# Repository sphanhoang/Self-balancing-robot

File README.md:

# Self-Balancing Robot with ESP32 and MPU6050

A comprehensive self-balancing robot implementation using ESP32 NodeMCU-32S board with GY-521 MPU6050 module, featuring FreeRTOS multi-tasking architecture, DMP (Digital Motion Processor) sensor fusion, and a real-time web interface for parameter tuning.

## 🚀 Features

- **FreeRTOS Multi-tasking Architecture**: Separate tasks for sensor reading, control, motor control, encoder reading, and web server
- **MPU6050 DMP Mode**: Uses Digital Motion Processor for accurate attitude estimation with quaternion-based sensor fusion
- **Dual PID Control System**: Roll (angle) and speed PID controllers with real-time parameter tuning
- **Real-time Web Interface**: Live parameter adjustment, data visualization, and robot control via WiFi
- **Encoder Feedback**: Quadrature encoder support for precise motor speed measurement
- **Safety Features**: Emergency stop, angle limits, and integral windup protection
- **Modular Design**: Easy to extend and modify with clear separation of concerns

## 📋 Hardware Requirements

### Main Components
- **ESP32 NodeMCU-32S** development board
- **GY-521 MPU6050** IMU module
- **Motor Driver** (L298N, TB6612FNG, or similar)
- **2x DC Motors** with quadrature encoders
- **Battery Pack** (7.4V - 12V recommended)
- **Robot Chassis** (3D printed or custom)

### Pin Connections

| ESP32 Pin | Component | Function |
|-----------|-----------|----------|
| GPIO 21   | MPU6050   | SDA (I2C) |
| GPIO 22   | MPU6050   | SCL (I2C) |
| GPIO 14   | Motor Driver | ENA (Right Motor PWM) |
| GPIO 32   | Motor Driver | ENB (Left Motor PWM) |
| GPIO 27   | Motor Driver | IN1 (Right Motor Direction) |
| GPIO 26   | Motor Driver | IN2 (Right Motor Direction) |
| GPIO 25   | Motor Driver | IN3 (Left Motor Direction) |
| GPIO 33   | Motor Driver | IN4 (Left Motor Direction) |
| GPIO 16   | Left Encoder | Channel A |
| GPIO 17   | Left Encoder | Channel B |
| GPIO 18   | Right Encoder | Channel A |
| GPIO 19   | Right Encoder | Channel B |

## 🏗️ Software Architecture

### FreeRTOS Task Structure

```
┌─────────────────┐    ┌─────────────────┐    ┌─────────────────┐
│   Sensor Task   │───▶│  Control Task   │───▶│   Motor Task    │
│   (Priority 5)  │    │  (Priority 4)   │    │  (Priority 3)   │
│  100Hz reading  │    │  100Hz control  │    │  100Hz update   │
└─────────────────┘    └─────────────────┘    └─────────────────┘
         │                       │                       │
         ▼                       ▼                       ▼
┌─────────────────┐    ┌─────────────────┐    ┌─────────────────┐
│  MPU6050 DMP    │    │  PID Controllers│    │  Motor Drivers  │
│  Sensor Fusion  │    │  Roll & Speed   │    │  PWM Control    │
└─────────────────┘    └─────────────────┘    └─────────────────┘
         │                       │                       │
         ▼                       ▼                       ▼
┌─────────────────┐    ┌─────────────────┐    ┌─────────────────┐
│  Encoder Task   │    │  Web Server     │    │  Monitor Task   │
│  (Priority 3)   │    │  (Priority 2)   │    │  (Priority 1)   │
│  1Hz reading    │    │  WiFi + HTTP    │    │  0.5Hz logging  │
└─────────────────┘    └─────────────────┘    └─────────────────┘
```

### Key Components

1. **Sensor Task**: Reads MPU6050 data using DMP mode with quaternion fusion
2. **Control Task**: Implements dual PID control (roll angle + speed) with web parameter updates
3. **Motor Task**: Controls motor speeds via MCPWM with direction control
4. **Encoder Task**: Reads quadrature encoders and calculates motor speeds
5. **Web Server Task**: Provides real-time web interface for parameter tuning and monitoring
6. **Monitor Task**: Logs system status and debugging information

## 🔧 Configuration

### PID Parameters (Tune for your robot)

```cpp
// Roll control (primary balancing)
#define KP_ROLL 18.0f     // Proportional gain (best results: 18)
#define KI_ROLL 50.0f     // Integral gain (best results: 50)
#define KD_ROLL 0.4f      // Derivative gain (best results: 0.4)

// Speed control (for forward/backward movement)
#define KP_SPEED 0.01f    // Proportional gain
#define KI_SPEED 0.01f    // Integral gain
#define KD_SPEED 0.01f    // Derivative gain
#define TILT_ANGLE 0.6f   // Target tilt angle for speed control
```

### Safety Limits

```cpp
#define MAX_MOTOR_SPEED 255.0f        // Maximum PWM value
#define MIN_MOTOR_SPEED 30.0f         // Minimum PWM value (38.25)
#define MAX_ANGLE 15.0f               // Normal operation limit (degrees)
#define MIN_ANGLE -15.0f              // Normal operation limit (degrees)
#define PWM_FREQ_HZ 100               // PWM frequency
```

### Web Interface Configuration

```cpp
#define CONFIG_WIFI_SSID "your_wifi_ssid"
#define CONFIG_WIFI_PASSWORD "your_wifi_password"
#define WEB_SERVER_PORT 80
```

## 🚀 Getting Started

### 1. Hardware Setup

1. **Connect MPU6050**:
   - VCC → 3.3V
   - GND → GND
   - SDA → GPIO 21
   - SCL → GPIO 22

2. **Connect Motor Driver**:
   - Connect motors to motor driver
   - Connect PWM and DIR pins to ESP32
   - Connect power supply

3. **Mount Components**:
   - Securely mount MPU6050 on robot chassis
   - Ensure MPU6050 is level when robot is balanced
   - Mount motors and wheels

### 2. Software Setup

1. **Install PlatformIO** (if not already installed)

2. **Clone/Download** this project

3. **Configure WiFi** (in `src/web_interface.cpp`):
   ```cpp
   #define CONFIG_WIFI_SSID "your_wifi_ssid"
   #define CONFIG_WIFI_PASSWORD "your_wifi_password"
   ```

4. **Build and Upload**:
   ```bash
   pio run -t upload
   ```

5. **Monitor Output**:
   ```bash
   pio device monitor
   ```

6. **Access Web Interface**:
   - Look for the IP address in the serial monitor output
   - Open your browser and navigate to `http://[robot_ip_address]`

### 3. Calibration

The system uses pre-calibrated MPU6050 offsets. You'll see:
```
I (xxxx) MPU6050: Testing device connections...
I (xxxx) MPU6050: MPU6050 connection successful
I (xxxx) MPU6050: Initializing DMP...
I (xxxx) MPU6050: DMP is ready!
```

## 🎛️ Tuning Guide

### Step 1: Basic Roll Control
1. Start with **KP_ROLL = 15.0f**
2. Gradually increase until robot shows response
3. Add **KD_ROLL = 0.3f** to reduce oscillations
4. Fine-tune for stability

### Step 2: Web Interface Tuning
1. Connect to the robot's web interface
2. Use the real-time sliders to adjust PID parameters
3. Monitor the live data chart for system response
4. Enable/disable balancing with the control button

### Step 3: Speed Control (Optional)
1. The system includes encoder feedback for speed control
2. Tune **KP_SPEED**, **KI_SPEED**, **KD_SPEED** for smooth movement
3. Adjust **TILT_ANGLE** for desired forward/backward tilt

### Step 4: Safety Tuning
1. Adjust **MAX_ANGLE** and **MIN_ANGLE** based on your robot's limits
2. Set appropriate **MIN_MOTOR_SPEED** to prevent stalling
3. Monitor the system through the web interface

## 🌐 Web Interface

The robot includes a comprehensive web interface accessible via WiFi:

### Features
- **Real-time Data Visualization**: Live charts showing angle and PID output
- **Parameter Tuning**: Sliders for adjusting PID parameters in real-time
- **Robot Control**: Enable/disable balancing with a single click
- **Status Monitoring**: Current angle, output values, and system status

### Access
1. Connect to the same WiFi network as configured in the code
2. Open your browser and navigate to the robot's IP address
3. Use the interface to tune parameters and monitor performance

### API Endpoints
- `GET /` - Main web interface
- `GET /data` - JSON data for real-time updates
- `GET /pid?kp_r=X&ki_r=Y&kd_r=Z` - Update PID parameters
- `GET /control?enable=1` - Enable/disable balancing

## 📊 Data Flow

### Sensor Data Structure
```cpp
typedef struct {
    float yaw, pitch, roll;        // Euler angles (degrees)
    float accel_x, accel_y, accel_z; // Linear acceleration (g)
    uint32_t timestamp;             // System timestamp
    float dt_since_last;            // Time delta since last reading
} sensor_data_t;
```

### Control Data Structure
```cpp
typedef struct {
    float roll_output;              // Roll PID output
    float speed_output;             // Speed PID output
    float left_motor_speed;         // Left motor PWM (-255 to 255)
    float right_motor_speed;        // Right motor PWM (-255 to 255)
    float left_motor_feedback;      // Left motor speed feedback (RPS)
    float right_motor_feedback;     // Right motor speed feedback (RPS)
    uint32_t timestamp;             // System timestamp
} control_data_t;
```

### Encoder Data Structure
```cpp
typedef struct {
    uint32_t left_encoder_pulseCount;   // Left encoder pulse count
    uint32_t right_encoder_pulseCount;  // Right encoder pulse count
    float left_motor_speed;             // Left motor speed (RPS)
    float right_motor_speed;            // Right motor speed (RPS)
} encoder_data_t;
```

### Web Control Structure
```cpp
typedef struct {
    float kp_roll, ki_roll, kd_roll;    // Roll PID parameters
    float kp_speed, ki_speed, kd_speed; // Speed PID parameters
    bool enable_balance;                 // Balance enable flag
    float target_angle;                  // Target tilt angle
} web_control_t;
```

## 🔍 Debugging

### Monitor Output
The system provides detailed logging:
```
I (xxxx) MPU: MPU6050 connection successful
I (xxxx) MPU: DMP is ready!
I (xxxx) WEB: Connect to: http://192.168.1.100
motor rps: LEFT: 2.1   RIGHT: 2.3
```

### Common Issues

1. **Robot falls immediately**:
   - Check MPU6050 orientation and mounting
   - Verify motor connections and polarity
   - Increase KP_ROLL gradually (start with 15.0)
   - Check if motors are responding correctly

2. **Oscillations**:
   - Reduce KP_ROLL
   - Increase KD_ROLL
   - Check for mechanical issues (loose connections)
   - Verify encoder readings are stable

3. **No response**:
   - Verify I2C connection (SDA/SCL pins)
   - Check motor driver power supply
   - Ensure proper WiFi configuration
   - Check serial monitor for error messages

4. **Web interface not accessible**:
   - Verify WiFi credentials in `web_interface.cpp`
   - Check if robot connected to WiFi (look for IP address in logs)
   - Ensure you're on the same network as the robot

5. **Encoder issues**:
   - Check encoder wiring (A/B channels)
   - Verify pull-up resistors are working
   - Check if encoder counts are incrementing in monitor output

## 🔌 PCB Design

The project includes a custom breakout board design in KiCad:

### Features
- **ESP32 NodeMCU-32S** mounting
- **MPU6050** module socket
- **Motor driver** connections (L298N compatible)
- **Encoder** input connectors
- **Power management** with voltage regulation
- **Debug headers** for easy testing

### Files
- `BreakoutBoard.kicad_pcb` - Main PCB layout
- `BreakoutBoard.kicad_sch` - Schematic design
- `Gerbers/` - Manufacturing files ready for PCB fabrication

### Usage
1. Order PCBs using the Gerber files
2. Solder components according to the schematic
3. Mount the ESP32 and MPU6050 modules
4. Connect motors and encoders to the appropriate headers

## 🛠️ Customization

### Adding Features

1. **Bluetooth Control**:
   - Add Bluetooth task alongside web server
   - Implement command parsing for mobile apps
   - Modify control task to accept external commands

2. **Enhanced Web Interface**:
   - Add data logging capabilities
   - Implement parameter persistence to flash
   - Add more sensor data visualization

3. **Data Logging**:
   - Add SD card support for data recording
   - Log sensor data for analysis
   - Export for MATLAB/Python analysis

4. **Advanced Control**:
   - Implement path following algorithms
   - Add obstacle avoidance
   - Implement remote control via web interface

### Motor Driver Support

The code supports various motor drivers through the `set_motor_speed()` function:

```cpp
void set_motor_speed(int motor, float speed) {
    // Current implementation supports L298N-style drivers
    // Easily adaptable for TB6612FNG, DRV8833, etc.
    // motor: 0 = right, 1 = left
    // speed: -255 to 255 (PWM value)
}
```

## 📚 Technical Details

### MPU6050 DMP Mode
- **Sample Rate**: 100Hz sensor reading
- **Fusion Algorithm**: Quaternion-based sensor fusion with gravity compensation
- **Output**: Direct Euler angles (yaw, pitch, roll) and linear acceleration
- **Calibration**: Pre-calibrated offsets for stable operation
- **DMP Features**: Built-in sensor fusion, FIFO buffer, interrupt support

### PID Control
- **Roll Control**: Primary balancing control using roll angle
- **Speed Control**: Forward/backward movement with encoder feedback
- **Anti-windup**: Integral term clamping to prevent windup
- **Derivative Filtering**: Prevents noise amplification
- **Real-time Tuning**: Parameters adjustable via web interface

### FreeRTOS Features
- **Task Priorities**: Sensor(5) > Control(4) > Motor(3) > Encoder(3) > Web(2) > Monitor(1)
- **Inter-task Communication**: Mutexes for data protection
- **Real-time Scheduling**: Deterministic timing with vTaskDelayUntil
- **Memory Management**: Optimized stack sizes for each task
- **Core Assignment**: All tasks run on Core 1 for consistency

### Motor Control
- **PWM Generation**: MCPWM hardware for precise motor control
- **Direction Control**: GPIO-based direction switching
- **Speed Range**: 30-255 PWM values with deadband protection
- **Encoder Feedback**: Quadrature encoder reading with interrupt handling

### Web Interface
- **HTTP Server**: Lightweight web server for parameter control
- **Real-time Updates**: 100ms refresh rate for live data
- **JSON API**: RESTful endpoints for data exchange
- **Responsive Design**: Works on desktop and mobile devices

## 🤝 Contributing

1. Fork the repository
2. Create a feature branch
3. Make your changes
4. Test thoroughly
5. Submit a pull request

## 📄 License

This project is open source. Feel free to use, modify, and distribute.

## 🙏 Acknowledgments

- **Jeff Rowberg** for the excellent MPU6050 library and DMP implementation
- **ESP-IDF** team for the robust FreeRTOS implementation and ESP32 support
- **InvenSense** for the MPU6050 sensor and DMP technology
- **PlatformIO** team for the excellent development environment
- **KiCad** community for the open-source PCB design tools

## 📞 Support

For questions and support:
- Check the debugging section above
- Review the code comments
- Open an issue on GitHub

---

**Happy Balancing! 🤖⚖️**

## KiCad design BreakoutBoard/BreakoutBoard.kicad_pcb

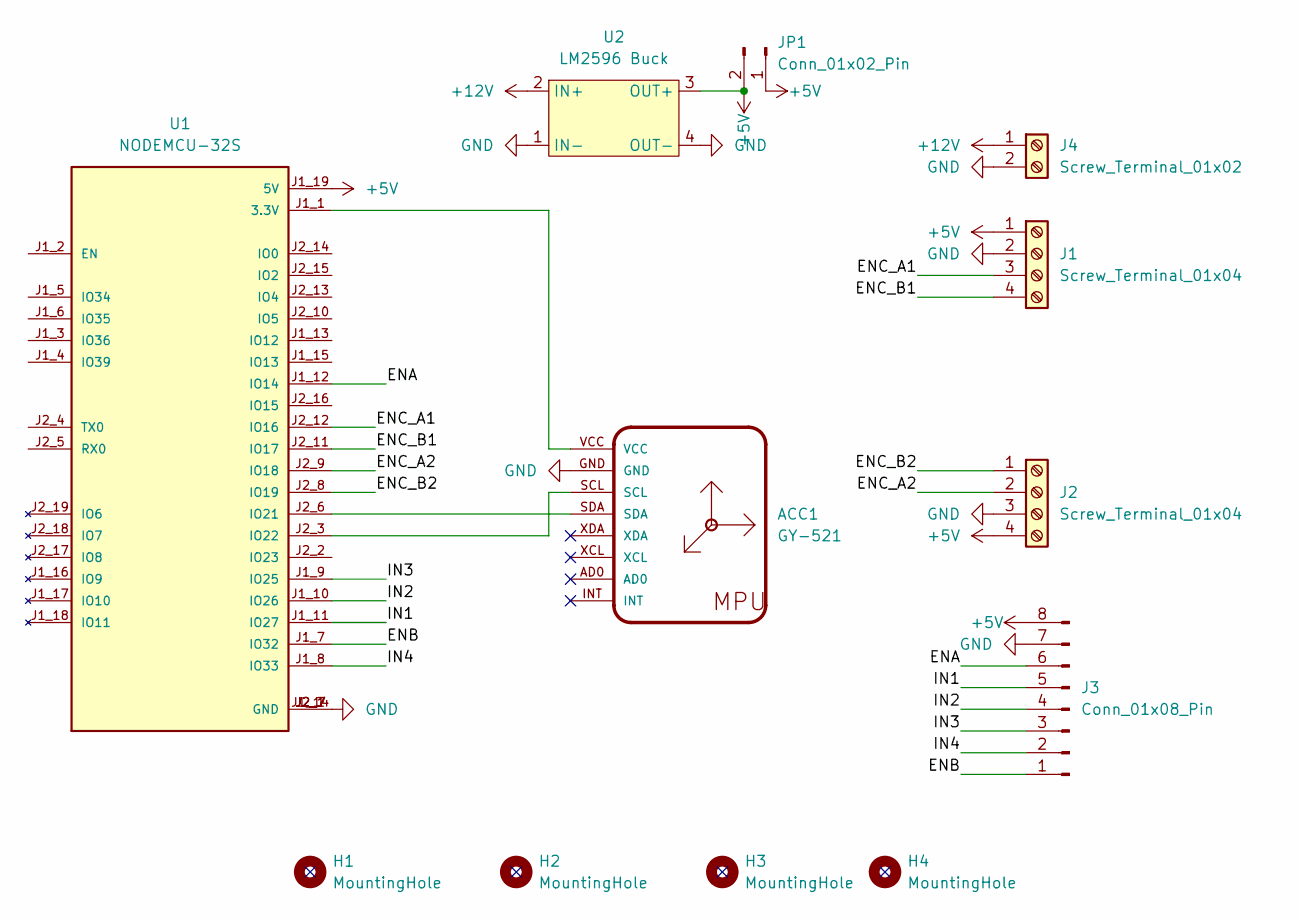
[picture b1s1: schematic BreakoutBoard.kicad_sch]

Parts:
ACC1: GY-521
H1, H2, H3, H4: MountingHole; MountingHole_3.2mm_M3_Pad
J1, J2: Screw_Terminal_01x04; ScrewTerminal_TB007-508-04BE
J3: Conn_01x08_Pin; PinHeader_1x08_P2.54mm_Vertical
J4: Screw_Terminal_01x02; ScrewTerminal_TB007-508-02BE
JP1: Conn_01x02_Pin; PinHeader_1x02_P2.54mm_Vertical
U1: NODEMCU-32S; ESP32-NODEMCU-32S; PARTREV V1
U2: LM2596 Buck; LM2596 WC00100 Module

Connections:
+5V: J1.1, J2.4, J3.8, JP1.1, JP1.2, U1.J1_19 (5V), U2.3 (OUT+)
+12V: J4.1, U2.2 (IN+)
/ENA: J3.6, U1.J1_12 (IO14)
/ENB: J3.1, U1.J1_7 (IO32)
/ENC_A1: J1.3, U1.J2_12 (IO16)
/ENC_A2: J2.2, U1.J2_9 (IO18)
/ENC_B1: J1.4, U1.J2_11 (IO17)
/ENC_B2: J2.1, U1.J2_8 (IO19)
/IN1: J3.5, U1.J1_11 (IO27)
/IN2: J3.4, U1.J1_10 (IO26)
/IN3: J3.3, U1.J1_9 (IO25)
/IN4: J3.2, U1.J1_8 (IO33)
GND: ACC1.GND, J1.2, J2.3, J3.7, J4.2, U1.J1_14 (GND), U1.J2_1 (GND), U1.J2_7 (GND), U2.1 (IN-), U2.4 (OUT-)
unnamed: ACC1.VCC, U1.J1_1 (3.3V)
unnamed: ACC1.SDA, U1.J2_6 (IO21)
unnamed: ACC1.SCL, U1.J2_3 (IO22)

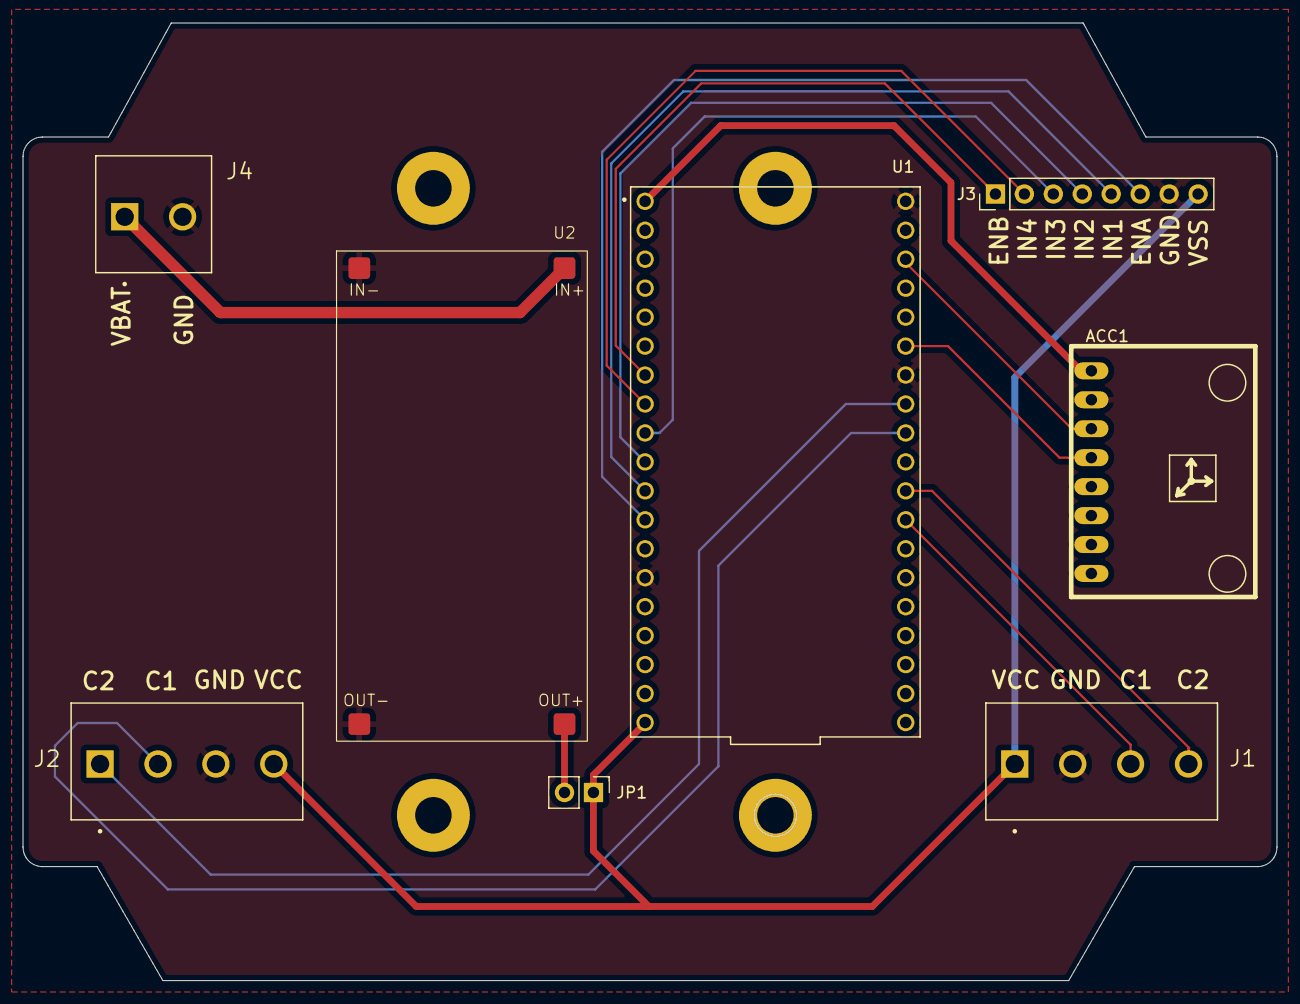
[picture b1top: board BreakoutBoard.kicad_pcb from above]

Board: 4 copper layers, 110.0 x 84.0 mm, 12 parts (0 on the bottom side), 16 nets.

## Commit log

2025-09-18 added breakout board schematic folder
2025-09-19 fixed various error. Sensor reading but no PWM
2025-09-19 init alt main
2025-09-20 drive motor using mcpwm lib
2025-09-20 lower PWM frequency for L298 driver to pickup low duty cycle
2025-09-20 update control_task logic
2025-09-20 added task templates.
2025-09-22 calib code for mpu-6050
2025-09-22 robot is running, need further PID tuning
2025-09-22 resolve wrong main.cpp after merge
2025-09-22 rename balance_robot.h header -> balancing_robot.h and refactor main.cpp for PID control
2025-09-23 refactor: improve PID controller structure and add mutex for sensor data access
2025-09-24 Lower I2C clock to fix DMP reading issue
2025-09-24 add encoder pin assignments
2025-09-24 first iteration for PID speed control
2025-09-25 move encoder reading to a seperate task
2025-09-25 Refactor: Remove LibDriverMPU6050 interface implementation
    - Deleted esp32_driver_mpu6050_interface.c as it is no longer needed.
    - Updated platformio.ini to remove references to LibDriverMPU6050 directories.
    - Modified main.cpp to include MPU6050 and MPU6050_6Axis_MotionApps20 headers.
    - Adjusted roll PID setpoint to 0.0f for better control.
    - Added web control functionality with a new web_interface.cpp file.
    - Implemented web server for real-time data visualization and PID tuning.
2025-09-30 Refactor: Update PID parameters and improve web interface functionality
2025-09-30 Refactor: Update PID parameters and remove web control header
